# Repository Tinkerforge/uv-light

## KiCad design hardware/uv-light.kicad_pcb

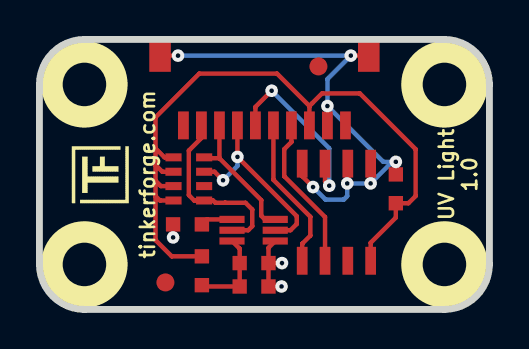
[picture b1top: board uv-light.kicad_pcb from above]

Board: 2 copper layers, 25.0 x 15.0 mm, 17 parts (2 on the bottom side), 10 nets.

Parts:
C1, C2: 100nF; C0603
C3: 10µF; C0603
Fiducial_Mark: VAL**; Fiducial_Mark
Fiducial_Mark#2: VAL**; Fiducial_Mark
P1: CON-SENSOR
R1: 270k; R0603
R2: 10; R0603
RP1: 2k2; 0603X4
U1: M24C64; SOIC8
U2: VEML6070; OPLGA6
U3, U4, U5, U6: DRILL; DRILL_NP
VAL: CE_5mm
VAL#2: WEEE_7mm_back

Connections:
GND: C1.1, C2.1, C3.1, P1.2, P1.EP, R1.2, U1.1, U1.2, U1.4, U2.1
unnamed: C2.2, C3.2, R2.1, U2.6
unnamed: P1.6, U1.3
unnamed: P1.7, RP1.7, U2.2
unnamed: P1.8, RP1.8, U2.3
unnamed: P1.9, RP1.5, U2.5
unnamed: R1.1, U2.4
SCL: P1.4, U1.6
SDA: P1.5, U1.5
VCC: C1.2, P1.3, R2.2, RP1.1, RP1.2, RP1.3, RP1.4, U1.8

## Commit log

2015-07-30 add uv light bricklet prototype
2015-07-30 Add readme
2015-08-12 add missing vcc connections
2015-08-13 change vcc routing
2015-08-24 define pullup value
2015-08-25 update to veml6070
2015-10-06 change resistor value to 240k
2015-10-06 Add initial implementation for veml6070
2015-10-06 change resistor value back to 270k
2015-10-06 Use formulas from app note to calculate µW/cm^2
2015-11-25 Include date and commit into changelog
2016-01-04 Add examples
2016-01-06 add schematic pdf
2016-01-07 Remove WIP marker
2016-01-07 Add .gitignore
2016-01-11 Update changelog
2016-01-11 Fix typo
2016-01-11 Remove accidentially added file
2016-05-18 c: Add missing device destroy call
2016-07-01 Make the change UID comment more explicit
2017-04-13 csharp: Adapt example
2017-04-21 shell: Adapt example
2017-06-02 octave: Use javaObject instead of deprecated java_new
2017-11-27 Add 3d information (final)
2017-11-27 Add 3d model (*.step & *.FCStd)
2017-11-30 Update examples from generator
2017-12-07 mathematica: Also generate .nb files
2018-01-26 c: Fine-tune printf format
2018-02-02 Update examples
2018-02-19 javascript: Close div tag correctly
2018-02-20 Cleanup KiCad libraries config
    Ensure LibDir=kicad-libraries and LibName1=tinkerforge.
    Remove special library.
2018-05-24 perl: Use strict in examples
2018-07-11 Add Makefile with docker support
2018-07-11 Remove obsolete generate_makefile scripts
2018-07-11 Update directory structure and build instructions
2018-07-26 Fix incorrect documentation about unit conversion
2018-09-14 examples: Fix wrong unit
2018-09-14 vbnet: Fix typo in comment
2018-11-06 Add rust examples
2018-11-07 rust: Accept host names for ip connection, fix naming inconsistencies
2018-11-07 rust: Rename callback receivers.
2018-12-14 Add go examples.
2018-12-14 go: Fix printf parameters.
2018-12-18 go: Change import path.
2018-12-18 go: Change import path again.
2018-12-20 rust: Reformat examples.
2019-01-24 mqtt: Add examples.
2019-01-24 mqtt: Fix example header.
2019-01-24 mqtt: Remove executable bit in example permissions.
2019-01-24 go: Minor example fixes.
2019-01-24 mqtt: Minor example fixes.
2019-03-28 mqtt: Fix whitespace.
2019-08-22 c: Adapt to bindings changes
2020-01-13 examples: Use python3 input instead of python2 raw_input.
2020-01-13 examples: mqtt: Remove trailing whitespace.
2020-04-14 mqtt: Fix device name format
2021-10-25 Update KiCad link
    https://www.kicad.org/blog/2021/10/Avoid-links-to-former-kicad-domain/
2022-07-06 Add license files.

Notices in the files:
hardware/uv-light.kicad_pcb:
Licensed under CERN OHL v.1.1
Copyright (©) 2015, B.Nordmeyer
Copyright Tinkerforge GmbH 2015.
This documentation describes Open Hardware and is licensed under the
CERN OHL v. 1.1.
